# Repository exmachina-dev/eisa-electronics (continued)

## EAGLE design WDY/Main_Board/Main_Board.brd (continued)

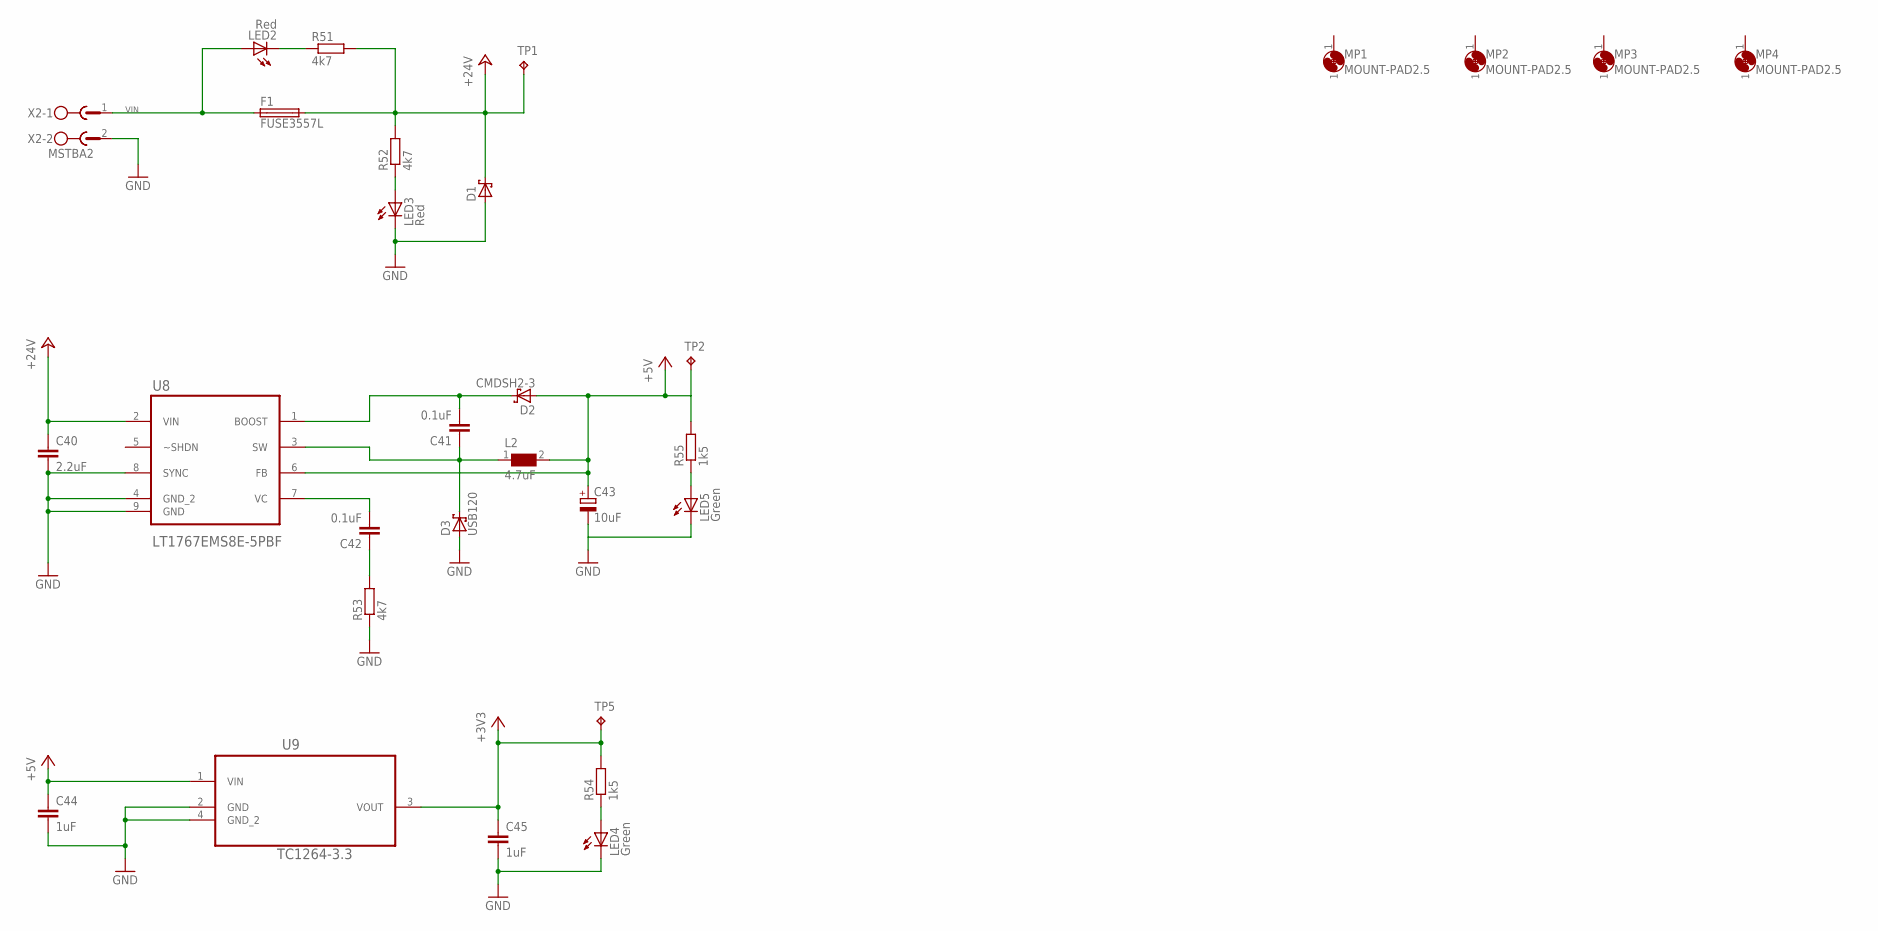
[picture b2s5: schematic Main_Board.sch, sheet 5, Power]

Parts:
C40: 2.2uF; C0603
C41, C42: 0.1uF; C0603
C43: 10uF; CT3216
C44, C45: 1uF; C0603
D1: STPS3L40UF; SMB
D2: CMDSH2-3; SOD323-W
D3: USB120; DO216AA
F1: FUSE3557L; 3557-LITTLE
L2: 4.7uF; WE-PD_1030/1050
LED2, LED3: Red; CHIPLED_0603
LED4, LED5: Green; CHIP-LED0603; MPN OVS-0604
MP1, MP2, MP3, MP4: MOUNT-PAD2.5; P2.5
R51, R52, R53: 4k7; R0603
R54, R55: 1k5; R0603; MPN MCMR06X1501FTL
TP1, TP2, TP5: TPB1,27; B1,27
U8: LT1767EMS8E-5PBF; SOP65P490X110-9N
U9: TC1264-3.3; SOT230P700X180-4N
X2: MSTBA2

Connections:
+3V3: C45.1, R54.2, TP5.TP, U9.3 (VOUT); also elsewhere on the board
+5V: C43.+, C44.1, D2.A, L2.2, R55.2, TP2.TP, U8.6 (FB), U9.1 (VIN); also elsewhere on the board
+24V: C40.1, D1.C, F1.3 (2), F1.4 (2), R51.2, R52.2, TP1.TP, U8.2 (VIN); also elsewhere on the board
GND: C40.2, C43.-, C44.2, C45.2, D1.A, D3.A, LED3.C, LED4.C, R53.1, U8.4 (GND_2), U8.8 (SYNC), U8.9 (GND), U9.2 (GND), U9.4 (GND_2), X2.2; also elsewhere on the board
GND1: LED5.C
unnamed: C41.2, D2.C, U8.1 (BOOST)
unnamed: LED3.A, R52.1
unnamed: LED2.C, R51.1
unnamed: C42.1, R53.2
unnamed: C42.2, U8.7 (VC)
unnamed: C41.1, D3.C, L2.1, U8.3 (SW)
unnamed: LED4.A, R54.1
unnamed: LED5.A, R55.1
VIN: F1.1, F1.2 (1), LED2.A, X2.1

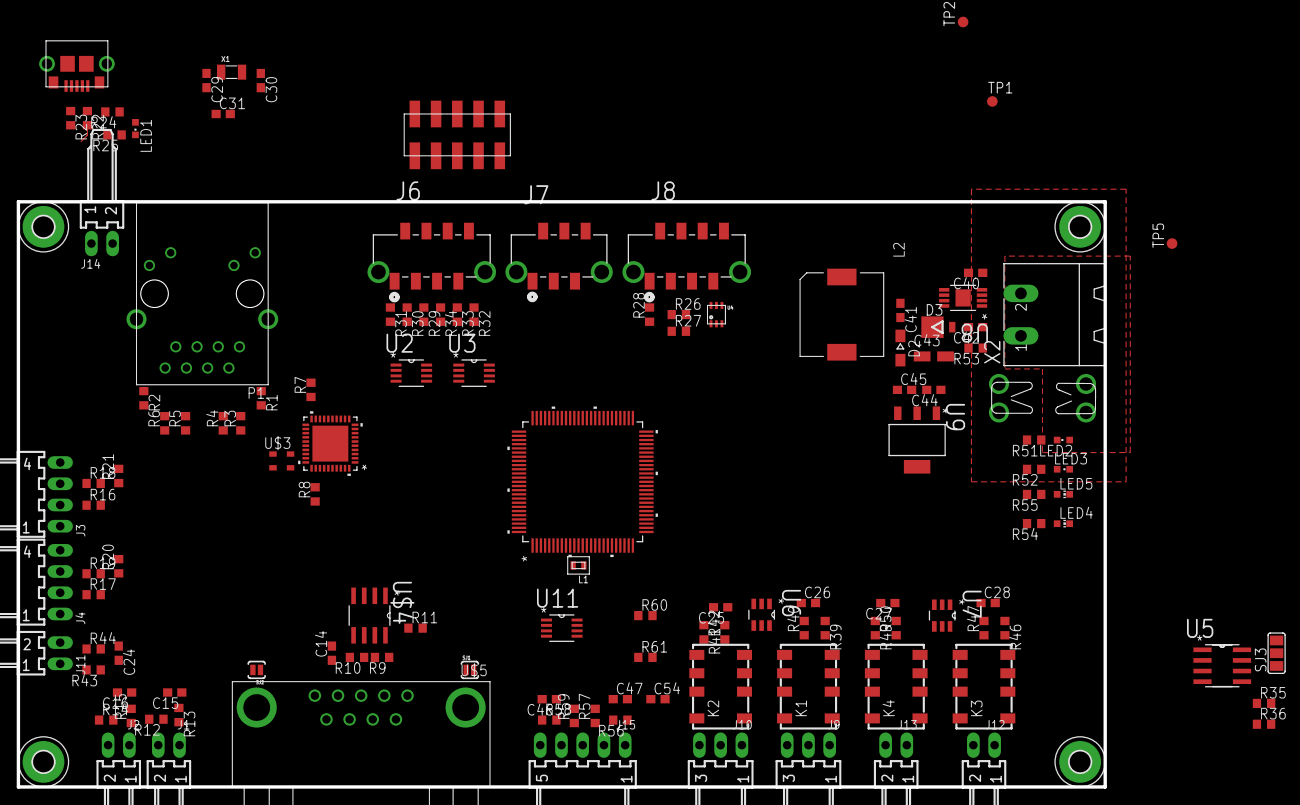
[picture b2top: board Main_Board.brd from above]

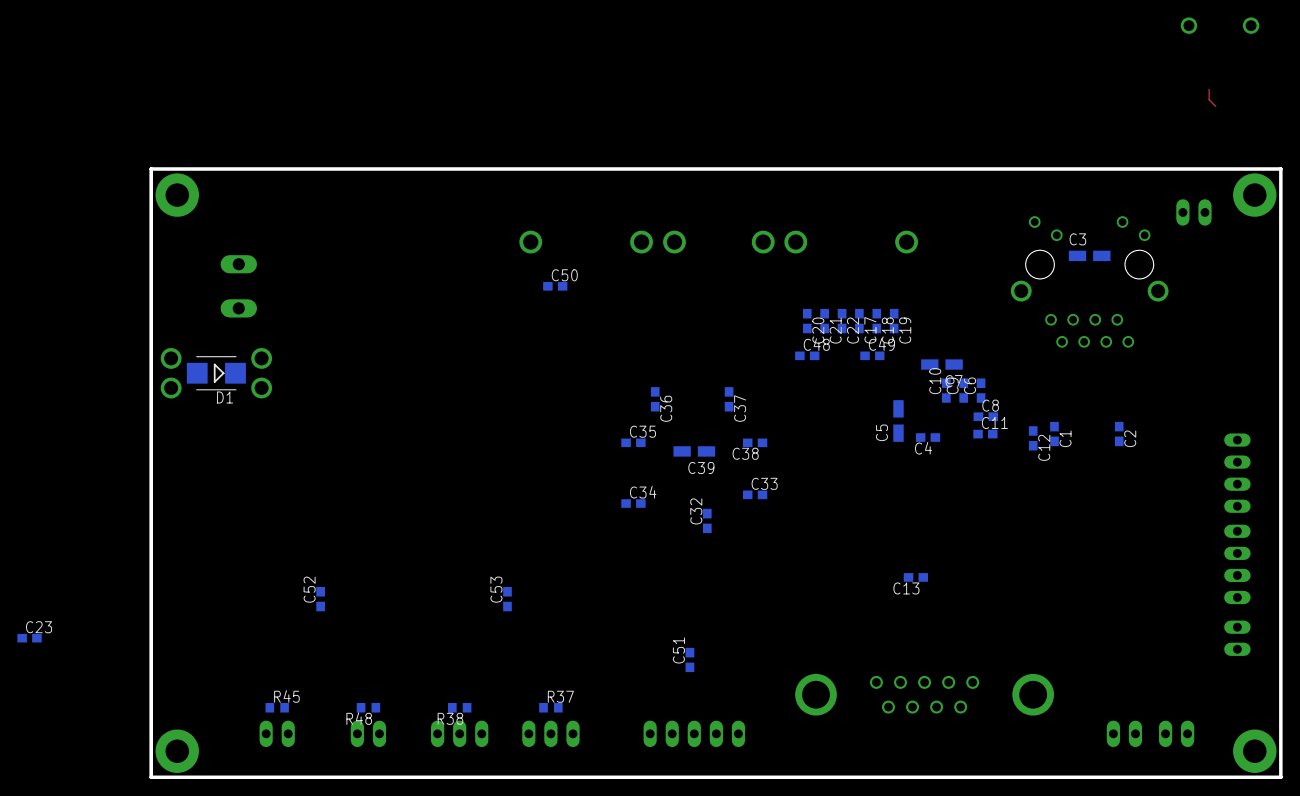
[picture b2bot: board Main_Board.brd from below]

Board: 4 copper layers, 130.0 x 70.0 mm, 174 parts (39 on the bottom side), 130 nets.

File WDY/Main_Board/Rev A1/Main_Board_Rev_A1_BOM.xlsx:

|  |  | Author | AB
 |  |  | Date | 42709
 |  |  | Rev | A1
Qty | Value | Device | Package | Parts | Description
1 | Green | LEDCHIPLED_0603 | CHIPLED_0603 | LED1 | LED
1 |  | STPS3L40UF | SMB | D1
31 | 0.1uF | C-EUC0603 | C0603 | C17, C18, C19, C20, C21, C22, C23, C24, C25, C26, C27, C28, C32, C33, C34, C35,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 | CAPACITOR, European symbol
1 | 0603PS-103KLB | 0603PS | 603 | L1
4 | 0R | R-EU_R0603 | R0603 | R68, R69, R71, R72 | RESISTOR, European symbol
19 | 100 | R-EU_R0603 | R0603 | R17, R18, R19, R37, R38, R40, R42, R45, R47, R48, R50, R57, R59, R60, R62, R63,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 | RESISTOR, European symbol
10 | 100nF | C-EUC0603 | C0603 | C1, C2, C4, C6, C8, C9, C10, C11, C12, C13 | CAPACITOR, European symbol
2 | 10K | R-EU_R0603 | R0603 | R11, R67 | RESISTOR, European symbol
6 | 10k | R-EU_R0603 | R0603 | R12, R13, R14, R15, R20, R21 | RESISTOR, European symbol
4 | 10uF | CPOL-EUCT3216 | CT3216 | C5, C7, C39, C43 | POLARIZED CAPACITOR, European symbol
1 | 1241050-5 | 1241050-5 | 2.54/2X5 | J5
2 | 18pF | C-EUC0603 | C0603 | C29, C30 | CAPACITOR, European symbol
1 | 1K | R-EU_R0603 | R0603 | R16 | RESISTOR, European symbol
6 | 1k | R-EU_R0603 | R0603 | R29, R30, R31, R32, R33, R34 | RESISTOR, European symbol
2 | 1k2 | R-EU_R0603 | R0603 | R73, R74 | RESISTOR, European symbol
2 | 1k5 | R-EU_R0603 | R0603 | R24, R25 | RESISTOR, European symbol
2 | 1k5 | R-EU_R0603 | R0603 | R54, R55 | RESISTOR, European symbol
2 | 1k8 | R-EU_R0603 | R0603 | R43, R44 | RESISTOR, European symbol
2 | 1uF | C-EUC0603 | C0603 | C44, C45 | CAPACITOR, European symbol
1 | 2.2uF | C-EUC0603 | C0603 | C40 | CAPACITOR, European symbol
5 | 22-05-7028-02 | 22-05-7028-02 | 2007041 | J1, J2, J12, J13, J14 | CONNECTOR
2 | 22-05-7038-03 | 22-05-7038-03 | 2007069 | J9, J10 | CONNECTOR
3 | 22-05-7048-04 | 22-05-7048-04 | 2007100 | J3, J4, J17 | CONNECTOR
1 | 22-05-7058-05 | 22-05-7058-05 | 2007130 | J15 | CONNECTOR
1 | 22-27-2061-06 | 22-27-2061-06 | 1647397 | J16 | CONNECTOR
2 | 220 | R-EU_R0603 | R0603 | R1, R2 | RESISTOR, European symbol
1 | 3000 | 3000 | 3000 | U$14
3 | 33 | R-EU_R0603 | R0603 | R22, R23, R28 | RESISTOR, European symbol
2 | 4.7uF | C-EUC0603 | C0603 | C15, C16 | CAPACITOR, European symbol
1 | 4.7uF | CPOL-EUCT3216 | CT3216 | C3 | POLARIZED CAPACITOR, European symbol
1 | 4.7uF | WE-PD-7447713047_1030/1050 | WE-PD_1030/1050 | L2 | SMD-Shielded Power Inductors WE-PD
1 | 4700pF | C-EUC0603 | C0603 | C14 | CAPACITOR, European symbol
4 | 49.9 | R-EU_R0603 | R0603 | R3, R4, R5, R6 | RESISTOR, European symbol
1 | 4K7 | R-EU_R0603 | R0603 | R8 | RESISTOR, European symbol
1 | 4K87 | R-EU_R0603 | R0603 | R7 | RESISTOR, European symbol
15 | 4k7 | R-EU_R0603 | R0603 | R26, R27, R35, R36, R39, R41, R46, R49, R51, R52, R53, R56, R58, R61, R66 | RESISTOR, European symbol
1 | 5504F1-09S-02A-03 | 5504F1-09S-02A-03 | 5504F1-09S-02A | U$5 | D-Sub 9pts, Righ-angle, solder
2 | 60 | R-EU_R0603 | R0603 | R9, R10 | RESISTOR, European symbol
1 | 90814-0206 | 90814-0206 | MOLEX_90814-0206 | J7 | CONN HEADER 06 POS 1.27MM SMD TIN
2 | 90814-0208 | 90814-0208 | MOLEX_90814-0208 | J6, J8 | CONN HEADER 8POS 1.27MM SMD TIN
1 | ASE-12 | ASE | ASE | U$10 | 3.3Vdc CMOS SMD CRYSTAL CLOCK OSCILLATOR
1 | ASE_50 | ASE | ASE | U$3 | 3.3Vdc CMOS SMD CRYSTAL CLOCK OSCILLATOR
1 | AT24C512C-SSHM-B | AT24C512C-SSHM-B | SOIC127P600X175-8N | U5 | SERIAL EEPROM IC Memory Size:512Kbit,8-SOIC
2 | B3FS-1015 | B3FS-1015 | B3FS | SW1, SW2 | Surface-mounting Switches Ideal for
1 | BC-2-P | BC-2-P | BC-2-P | JP1
1 | CMDSH2-3 | CMDSH2-3 | SOD323-W | D2
1 | DP83848JSQ/NOPB | DP83848JSQ/NOPB | SQA40B | U$2
1 | FC-135 | FC-135 | FC-135 | X1 | 32.768kHz ±20ppm Crystal 12.5pF 70 kOhm -40°C ~ 85°C Surface Mount 2-SMD
1 | FTSH-105-01-L-DV | FTSH-105-01-L-DV | FTSH-105-01-L-DV | J11
1 | FUSE3557L | FUSE3557L | 3557-LITTLE | F1 | Fuse
4 | G6K-2G-Y | G6K-2G-Y | G6K-2G-Y | K1, K2, K3, K4 | Low Signal Relay
2 | Green | LEDCHIP-LED0603 | CHIP-LED0603 | LED4, LED5 | LED
1 | LPC1768FBD100 | LPC1768FBD100 | SOT407-1 | U1
1 | LT1767EMS8E-5PBF | LT1767EMS8E-5PBF | SOP65P490X110-9N | U8 | Step-Down Switching Regulators
1 | MCP2561-E/SN | MCP2561-E/SN | SOIC127P600X175-8N | U$4 | High-Speed CAN Transceiver
1 | MMBT2222AL | MMBT2222AL | SOT-23 | T1 | General Purpose Transistors
1 | MSTBA2 | MSTBA2 | MSTBA2 | X2 | PHOENIX
1 | RB1-125BAG1A | RB1-125BAG1A | WIZNET_RB1-125BAG1A | P1 | Accessory RJ-45 With Transformer Connector - UDE
2 | Red | LEDCHIPLED_0603 | CHIPLED_0603 | LED2, LED3 | LED
2 | SN74LVC2G17DBVR | SN74LVC2G17DBVR | SOT95P280X145-6N | U6, U7 | DUAL SCHMITT-TRIGGER BUFFER
3 | SN74LVC3G17DCTR | SN74LVC3G17DCTR | SOP65P400X130-8N | U2, U3, U11 | TRIPLE SCHMITT-TRIGGER BUFFER
1 | TC1264-3.3 | TC1264-3.3 | SOT230P700X180-4N | U9 | IC, 8
1 | TLV313 | TLV313 | SOT23-DBV | U10
1 | TPL0401A | TPL0401A | SC-70-DCK | U4
1 | USB120 | USB120 | DO216AA | D3
1 | USB3075-30-A | USB3075-30-A | USB_MICROB_SMT | U$6

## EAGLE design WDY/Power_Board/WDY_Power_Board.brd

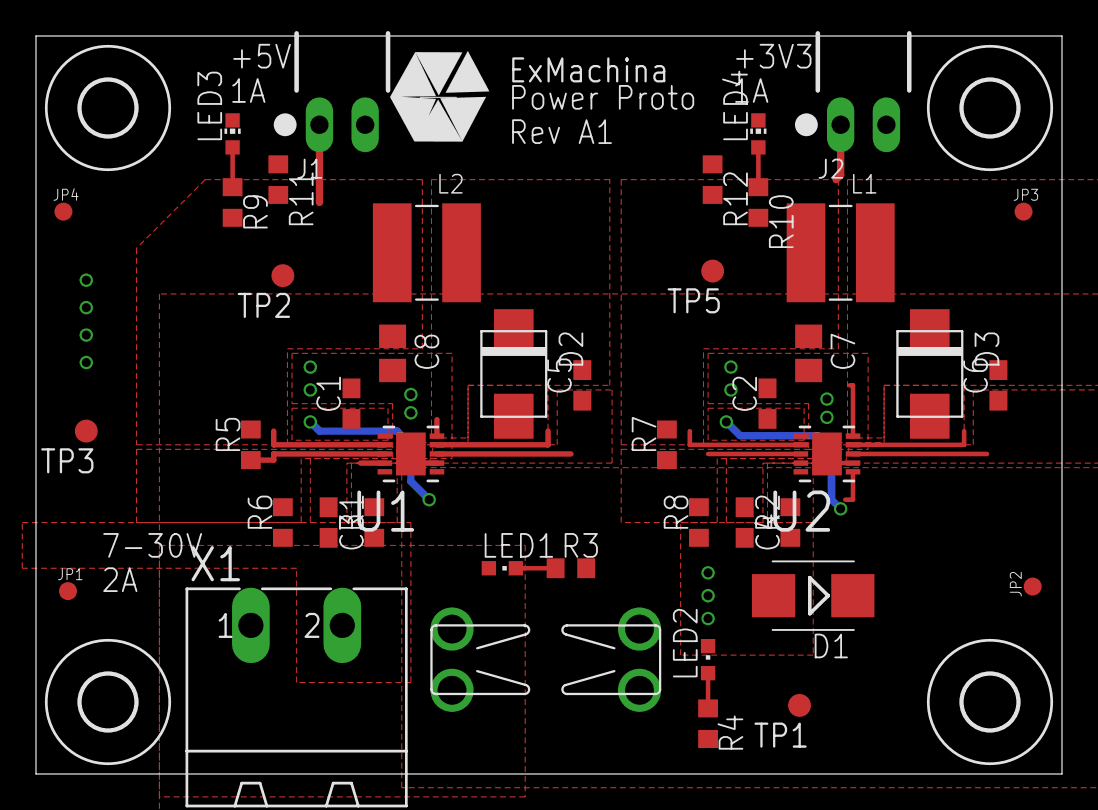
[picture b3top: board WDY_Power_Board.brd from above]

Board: 2 copper layers, 57.0 x 41.0 mm, 48 parts (0 on the bottom side), 21 nets.

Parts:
C1, C2, C5, C6: 2.2uF; C0603
C3, C4: 1000pF; C0603
C7, C8: 22uF; C0805
D1: STPS3L40UF; SMB
D2, D3: MBRS140; DO-214AA
F1: FUSE3557L; 3557-LITTLE
H1, H2, H3, H4: MOUNT-HOLE3.0; 3,0
J1, J2: 22-05-7028-02; 7395-02
JP1, JP2, JP3, JP4: FIDUCIAL1X2; FIDUCIAL-1X2
L1: 10uH; WE-PD2_5848/5820
L2: 15uH; WE-PD2_5848/5820
LED1, LED2: Blue; CHIPLED_0603
LED3, LED4: Blue; CHIP-LED0603
R1, R2, R7: 31k6; R0603
R3, R4: 4k7; R0603
R5: 52k3; R0603
R6, R8: 10k; R0603
R9, R10, R11, R12: 1k5; R0603
TP1, TP2, TP3, TP5: TPB1,27; B1,27
U1, U2: LT3686HDDPBF; DFN300X300X80-11N
U$1: EXMACHINA-LOGO-NAME; EXM-LOGO-BASELINE
X1: MSTBA2

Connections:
+3V3: C7.1, J2.1, L1.2, R7.2, R10.2, R12.2, TP5.TP, U2.2
+5V: C8.1, J1.1, L2.2, R5.2, R9.2, R11.2, TP2.TP, U1.2
+24V: C1.1, C2.1, D1.C, F1.3, F1.4, R3.2, R4.2, TP1.TP, U1.1, U1.6, U2.1, U2.6
GND: C1.2, C2.2, C3.2, C4.2, C7.2, C8.2, D1.A, J1.2, J2.2, LED2.C, LED3.C, LED4.C, R1.1, R2.1, R6.1, R8.1, R11.1, R12.1, TP3.TP, U1.7, U1.11, U2.7, U2.11, X1.2
unnamed: R1.2, U1.5
unnamed: R7.1, R8.2, U2.3
unnamed: C3.1, U1.4
unnamed: R2.2, U2.5
unnamed: C4.1, U2.4
unnamed: R5.1, R6.2, U1.3
unnamed: C6.1, U2.8
unnamed: C5.1, U1.8
unnamed: C5.2, D2.C, L2.1, U1.10
unnamed: D2.A, U1.9
unnamed: C6.2, D3.C, L1.1, U2.10
unnamed: D3.A, U2.9
unnamed: LED2.A, R4.1
unnamed: LED1.C, R3.1
unnamed: LED4.A, R10.1
unnamed: LED3.A, R9.1
VIN: F1.1, F1.2, LED1.A, X1.1
